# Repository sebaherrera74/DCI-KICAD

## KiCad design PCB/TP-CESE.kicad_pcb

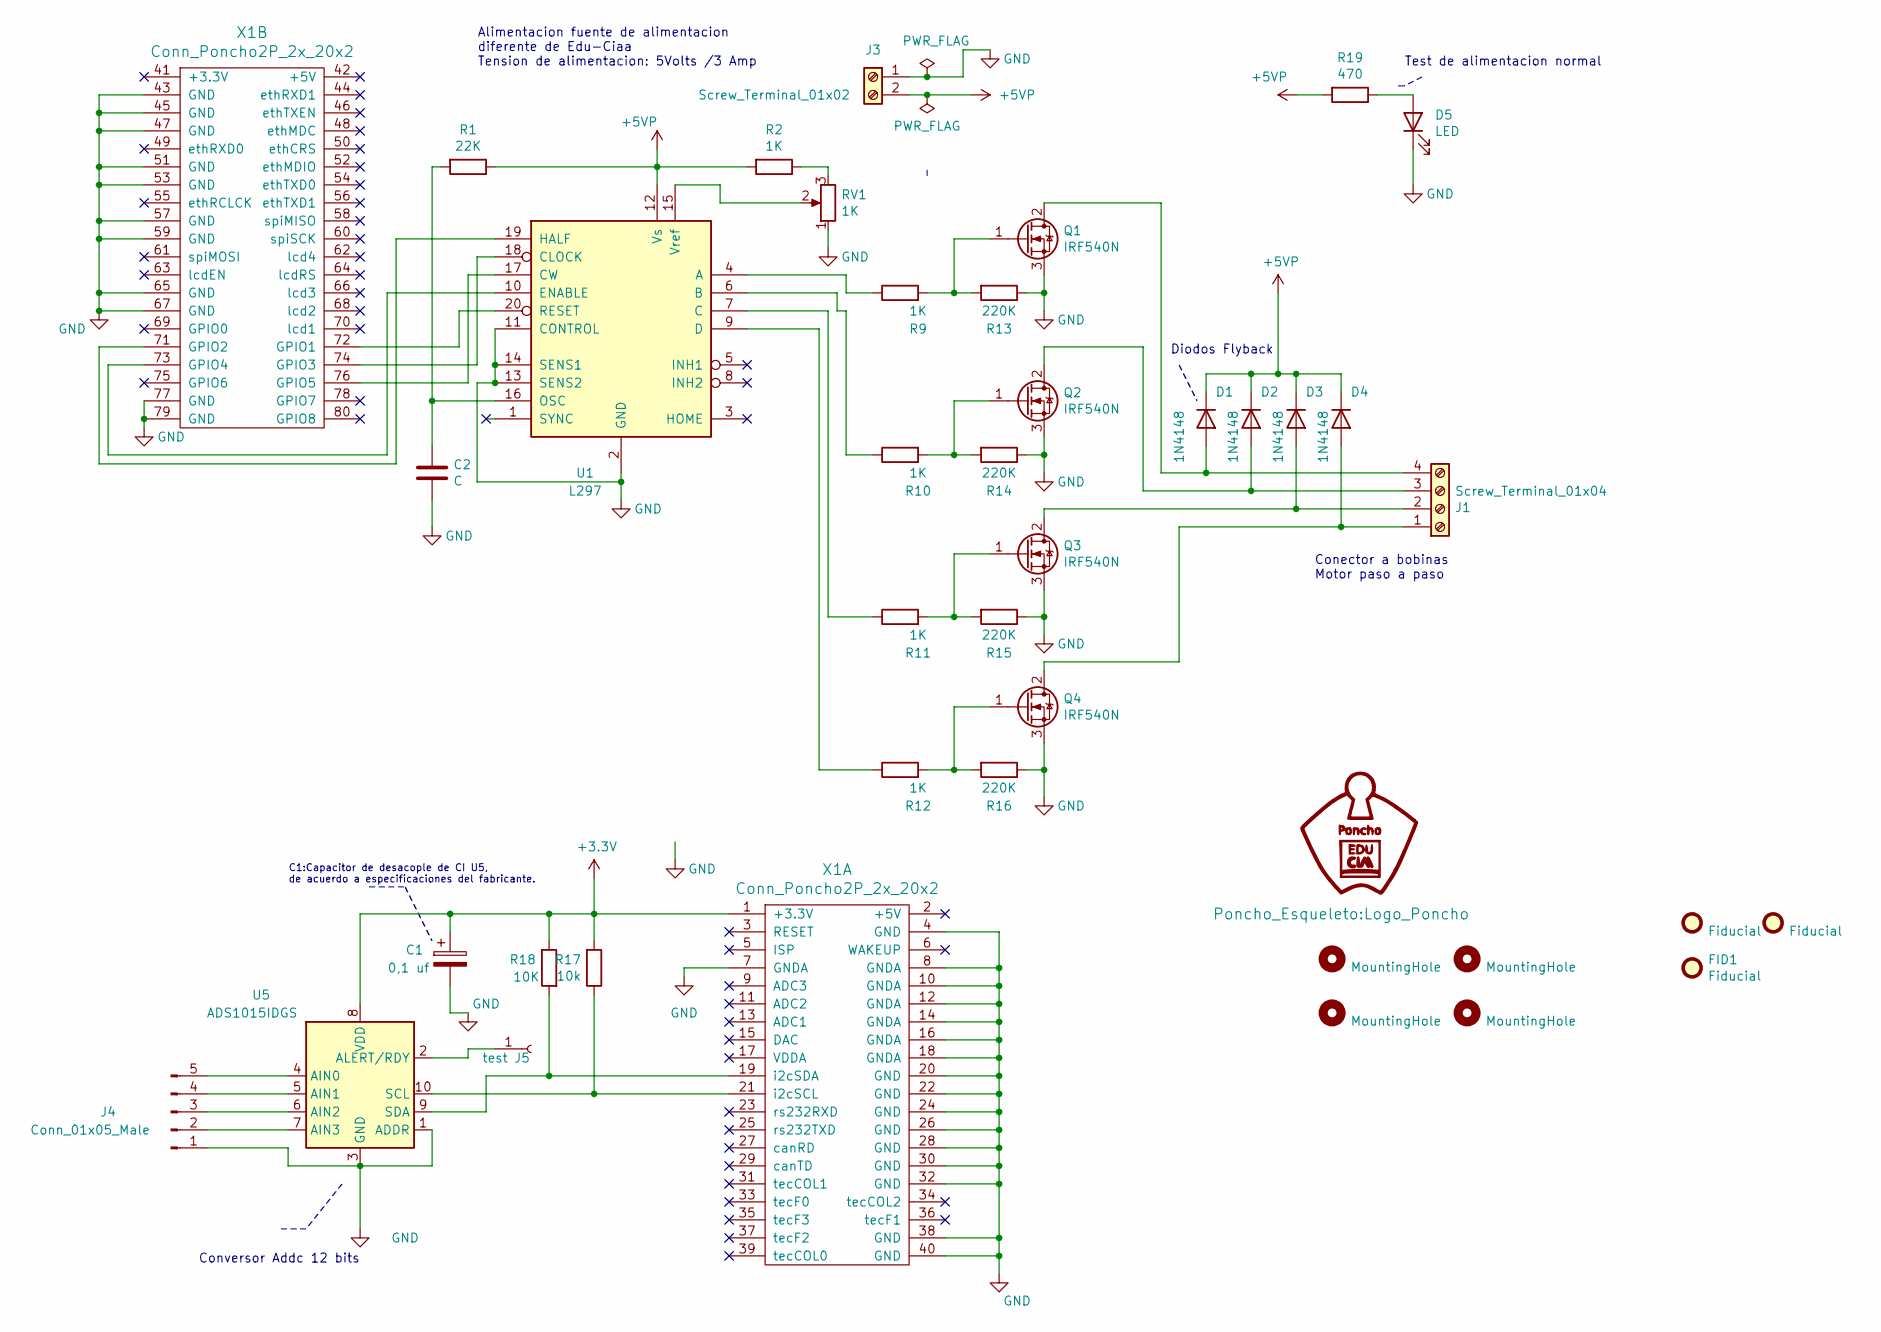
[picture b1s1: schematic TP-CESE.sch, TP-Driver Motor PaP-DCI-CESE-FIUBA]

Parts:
C1: 0,1 uf; C_0805_2012Metric
C2: C; C_Disc_D3.0mm_W1.6mm_P2.50mm
D1, D2, D3: 1N4148; D_DO-35_SOD27_P7.62mm_Horizontal; Digikey# 1N4148FS-ND
D4: 1N4148; D_DO-35_SOD27_P7.62mm_Horizontal; digikey# 1N4148FS-ND
D5: LED; LED_D3.0mm_Clear
FID1, FID2, FID3: Fiducial; Fiducial_1mm_Mask2mm
H1, H2, H3, H4: MountingHole; MountingHole_2.2mm_M2_DIN965_Pad
J1: Screw_Terminal_01x04; TerminalBlock_Phoenix_MKDS-1,5-4-5.08_1x04_P5.08mm_Horizont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
J3: Screw_Terminal_01x02; TerminalBlock_Phoenix_MKDS-1,5-2-5.08_1x02_P5.08mm_Horizont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
J4: Conn_01x05_Male; PinHeader_1x05_P2.00mm_Vertical
J5: test; PinHeader_1x01_P2.00mm_Vertical
Q1: IRF540N; TO-262-3_Vertical; digikey# IRF540NLPBF-ND
Q2, Q3, Q4: IRF540N; TO-262-3_Vertical; Digikey# IRF540NLPBF-ND
R1: 22K; R_Axial_DIN0207_L6.3mm_D2.5mm_P7.62mm_Horizontal
R2, R9, R10, R11, R12: 1K; R_Axial_DIN0207_L6.3mm_D2.5mm_P7.62mm_Horizontal
R13, R14, R15, R16: 220K; R_Axial_DIN0207_L6.3mm_D2.5mm_P7.62mm_Horizontal
R17: 10k; R_Axial_DIN0207_L6.3mm_D2.5mm_P7.62mm_Horizontal
R18: 10K; R_Axial_DIN0207_L6.3mm_D2.5mm_P7.62mm_Horizontal
R19: 470; R_Axial_DIN0207_L6.3mm_D2.5mm_P7.62mm_Horizontal
RV1: 1K; Potentiometer_Bourns_3299W_Vertical
U1: L297; DIP-20_W7.62mm_Socket_LongPads
U5: ADS1015IDGS; TSSOP-10_3x3mm_P0.5mm; Digikey# 296-41185-1-ND
X1: Conn_Poncho2P_2x_20x2; Conn_Poncho_Chico

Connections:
+3V3: C1.1, R17.2, R18.1, U5.8 (VDD), X1.1 (+3.3V)
+5VP: D1.1 (K), D2.1 (K), D3.1 (K), D4.1 (K), J3.2, R1.1, R2.2, R19.2, U1.12 (Vs)
GND: C1.2, C2.2, D5.1 (K), J3.1, J4.1, Q1.3 (S), Q2.3 (S), Q3.3 (S), Q4.3 (S), R13.1, R14.1, R15.1, R16.1, RV1.1, U1.2 (GND), U1.11 (CONTROL), U1.13 (SENS2), U1.14 (SENS1), U5.1 (ADDR), U5.3 (GND), X1.4 (GND), X1.7 (GNDA), X1.8 (GNDA), X1.10 (GNDA), X1.12 (GNDA), X1.14 (GNDA), X1.16 (GNDA), X1.18 (GNDA), X1.20 (GND), X1.22 (GND), X1.24 (GND), X1.26 (GND), X1.28 (GND), X1.30 (GND), X1.32 (GND), X1.38 (GND), X1.40 (GND), X1.43 (GND), X1.45 (GND), X1.47 (GND), X1.51 (GND), X1.53 (GND), X1.57 (GND), X1.59 (GND), X1.65 (GND), X1.67 (GND), X1.77 (GND), X1.79 (GND)
unnamed: C2.1, R1.2, U1.16 (OSC)
unnamed: D1.2 (A), J1.4, Q1.2 (D)
unnamed: D2.2 (A), J1.3, Q2.2 (D)
unnamed: D3.2 (A), J1.2, Q3.2 (D)
unnamed: D4.2 (A), J1.1, Q4.2 (D)
unnamed: D5.2 (A), R19.1
unnamed: J4.2, U5.7 (AIN3)
unnamed: J4.3, U5.6 (AIN2)
unnamed: J4.4, U5.5 (AIN1)
unnamed: J4.5, U5.4 (AIN0)
unnamed: J5.1, U5.2 (ALERT/RDY)
unnamed: Q1.1 (G), R9.2, R13.2
unnamed: Q2.1 (G), R10.2, R14.2
unnamed: Q3.1 (G), R11.2, R15.2
unnamed: Q4.1 (G), R12.2, R16.2
unnamed: R2.1, RV1.3
unnamed: R9.1, U1.4 (A)
unnamed: R10.1, U1.6 (B)
unnamed: R11.1, U1.7 (C)
unnamed: R12.1, U1.9 (D)
unnamed: R17.1, U5.10 (SCL), X1.21 (i2cSCL)
unnamed: R18.2, U5.9 (SDA), X1.19 (i2cSDA)
unnamed: RV1.2, U1.15 (Vref)
unnamed: U1.10 (ENABLE), X1.73 (GPIO4)
unnamed: U1.17 (CW), X1.76 (GPIO5)
unnamed: U1.18 (CLOCK), X1.74 (GPIO3)
unnamed: U1.19 (HALF), X1.71 (GPIO2)
unnamed: U1.20 (RESET), X1.72 (GPIO1)

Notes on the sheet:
Conector a bobinas Motor paso a paso
Alimentacion fuente de alimentacion diferente de Edu-Ciaa Tension de alimentacion: 5Volts /3 Amp
Conversor Addc 12 bits
Diodos Flyback
Test de alimentacion normal
C1:Capacitor de desacople de CI U5, de acuerdo a especificaciones del fabricante.

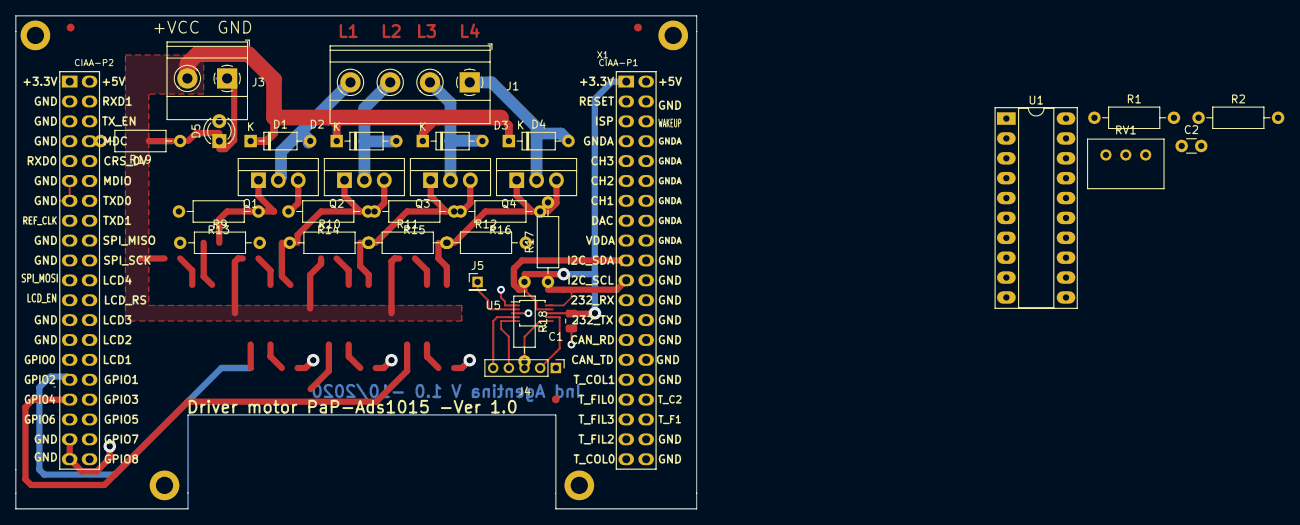
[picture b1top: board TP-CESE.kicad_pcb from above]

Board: 2 copper layers, 87.0 x 63.0 mm, 39 parts (0 on the bottom side), 31 nets.

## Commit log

2020-09-18 Primer Commit
2020-09-18 Hoja de Datos
2020-09-18 Agrego carpetas de acuerdo a pautas para la practica final
2020-09-24 Agrego libreria poncho de edu-ciaa y hojas de datos
2020-09-25 Conexiones, diodos de protecccion
2020-10-02 agrego huellas, hojas de datos de diodo y tabla de potencia de resistencia smd
2020-10-08 Correcciones Charlie , agrego hojas de datos
2020-10-15 Correciones al esquematico, de acuerdo a sugerencia de Diego Brengi(Profesor) y Carlos Carreño Romano(revisor)
2020-10-15 Posicionamiento de componenetes en PCB
2020-10-25 Ubicacion de componentes y ruteados
2020-10-25 Gerbers, Bom ,mejoro conexiones
2020-10-25 Carpeta Shapes3D
2020-10-29 Correcciones Realizadas
2021-01-15 Se agrga integrado L297 , para manejo de motor paso a paso, se sacan los optoacopladores ya que el L297 maneja directamente los Irf
